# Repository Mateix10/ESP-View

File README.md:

# ESP-View
This is a music visualiser + DAC that does exactly that - it plays the music through USB, and visualises it.

<sub>Also, a better name will be much appreciated :)</sub>

## PCB
The PCB is designed in kicad.

## Case
The case features a screw and a little groove where the PCB slides.
It has a slick, modern, round design.

Designed in Fusion 360.

## Firmware 
The whole thing is powered by a ESP32, paired with a PCM5102A DAC.
The firmware is written in Arduino IDE

To interface with the ESP32, you need to install board support in Arduino IDE.
You can do that by going to File -> Preferences -> Additional Board Manager URLs, and add https://espressif.github.io/arduino-esp32/package_esp32_index.json

After that, go to Tools -> Board -> Boards Manager. Search for esp32 and install "esp32" by Espressif.

**WARNING**: Version 3.x is required for proper TinyUSB audio support.

Required libraries:
- NeoPixelBus by Makuna
- arduinoFFT
- TinyUSB (Usually bundled with the EPS32 Arduino Core)

All of these can be installed through the Arduino IDE's library manager.

The Firmware isn't currently tested.

## BOM
| Name | Cost |Link|
|--------|--------|--------|
| 1000uF Electrolytic Capacitor | $0.48 |https://www.optimusdigital.ro/ro/componente-electronice-condensatoare/3004-condensator-electrolitic-de-1000-uf-la-35-v.html|
| LED Matrix | $24.98 |https://www.superlightingled.com/5v-16x16-sk6812-rgbw-led-neopixel-matrix-display-screen-panel-51w-p-6835.html|
| DAC | $22.80 |https://www.optimusdigital.ro/ro/audio-altele/5658-modul-audio-stereo-dac-pcm5102a-cu-interfaa-pcm-32-bii-384-khz.html|
| Level Shifter| $3.19 |https://www.aliexpress.com/item/1005007123530432.html|
|ESP32-S3-DevKitC-1| $18.50 |https://www.aliexpress.com/item/1005003979778978.html|
|PCB|$1.74|-|

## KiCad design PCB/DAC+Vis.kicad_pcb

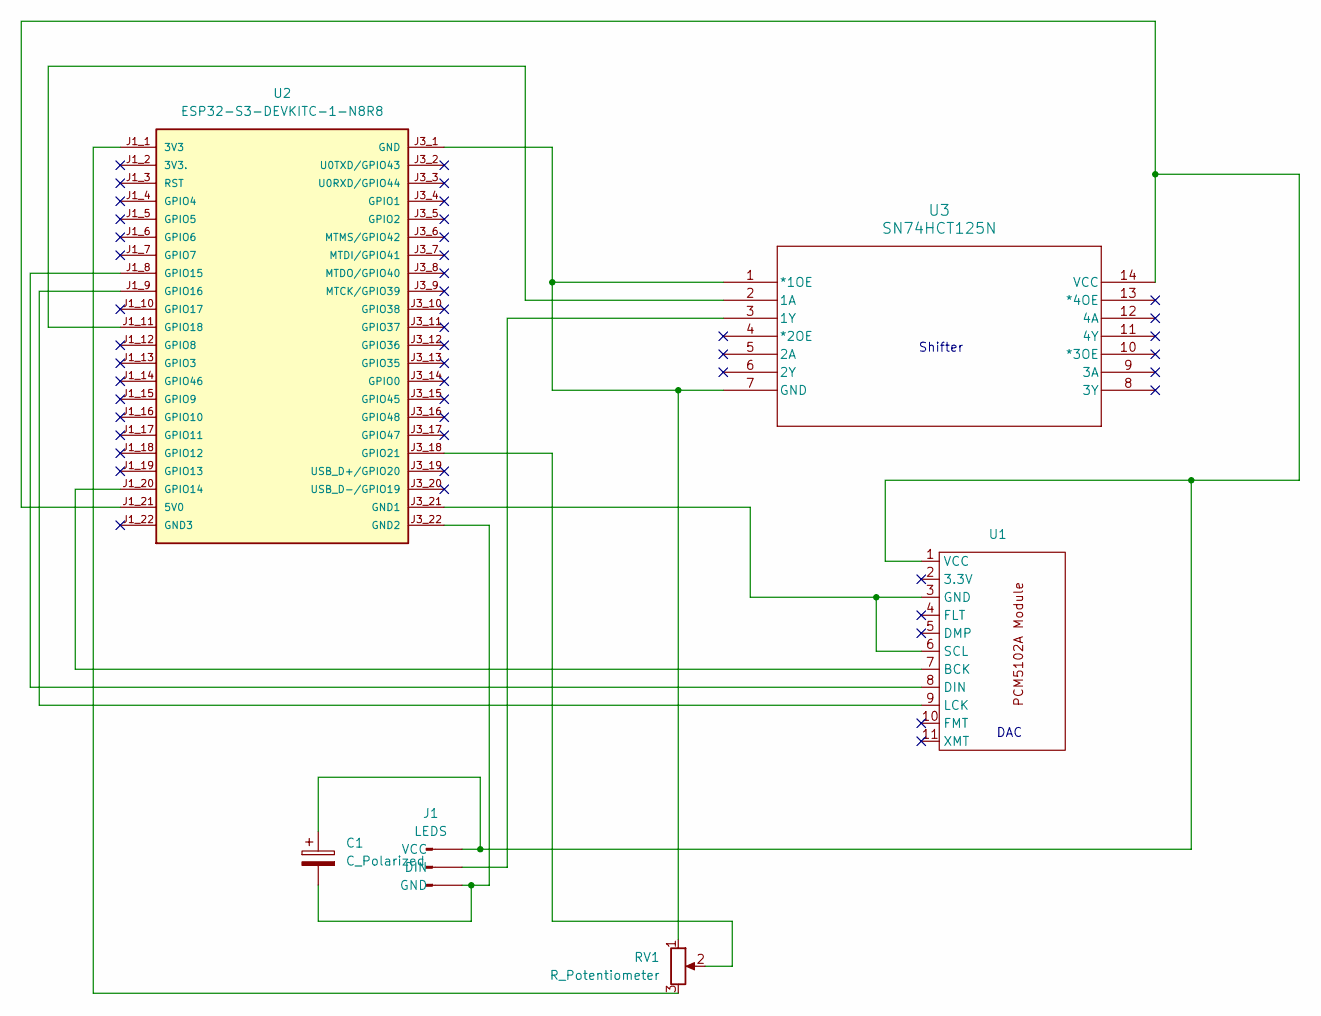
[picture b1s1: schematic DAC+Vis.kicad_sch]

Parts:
C1: C_Polarized; CP_Radial_D10.0mm_P5.00mm
J1: LEDS; SolderWire-4sqmm_1x03_P12mm_D3mm_OD6mm
RV1: R_Potentiometer; Potentiometer_Alps_RK097_Single_Horizontal
U1: PCM5102A Module
U2: ESP32-S3-DEVKITC-1-N8R8
U3: SN74HCT125N; N14

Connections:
unnamed: J1.2 (DIN), U3.3 (1Y)
unnamed: C1.2, J1.3 (GND), U2.J3_22 (GND2)
unnamed: C1.1, J1.1 (VCC), U1.1 (VCC), U2.J1_21 (5V0), U3.14 (VCC)
unnamed: U1.7 (BCK), U2.J1_20 (GPIO14)
unnamed: U1.8 (DIN), U2.J1_8 (GPIO15)
unnamed: U1.3 (GND), U1.6 (SCL), U2.J3_21 (GND1)
unnamed: U1.9 (LCK), U2.J1_9 (GPIO16)
unnamed: RV1.3, U2.J1_1 (3V3)
unnamed: RV1.1, U2.J3_1 (GND), U3.1 (*1OE), U3.7 (GND)
unnamed: U2.J1_11 (GPIO18), U3.2 (1A)
unnamed: RV1.2, U2.J3_18 (GPIO21)

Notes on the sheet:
Shifter
DAC

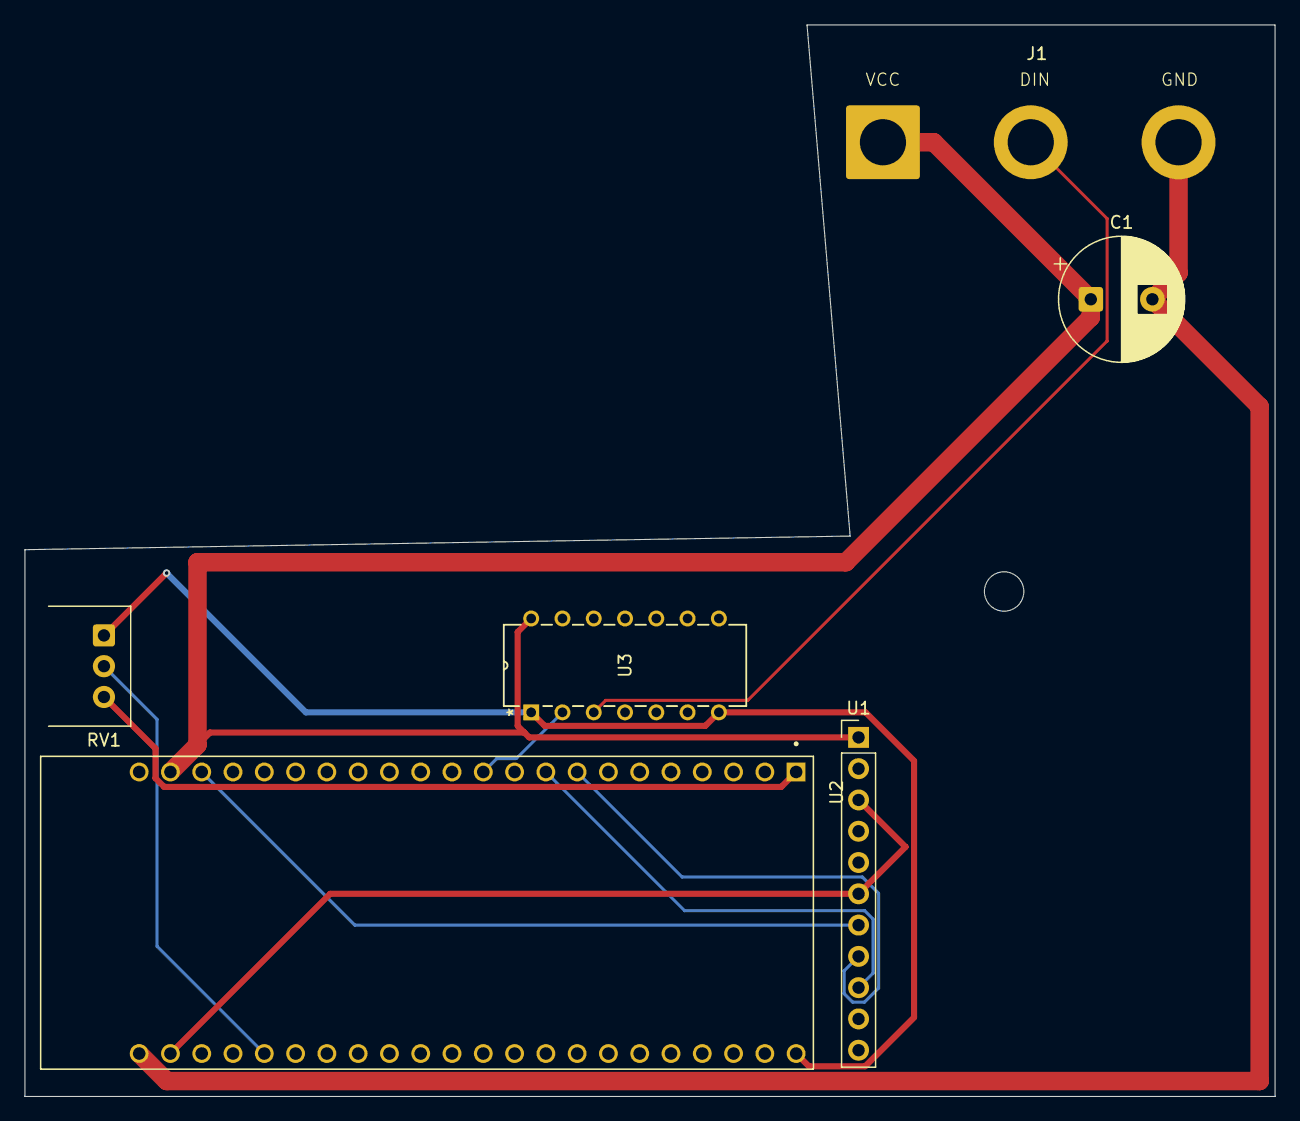
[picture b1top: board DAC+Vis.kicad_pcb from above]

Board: 2 copper layers, 101.5 x 87.0 mm, 6 parts (0 on the bottom side), 11 nets.

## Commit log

2026-03-09 Update .gitignore to add macOS files
    Added macOS system files.
2026-03-18 Enhance README with project details and specifications
    Added detailed description of the project, including case design and hardware specifications.
2026-03-18 Fix typo in README regarding ESP32 description
2026-03-18 Added images
2026-03-18 Added images to README
2026-03-18 Added image in README
2026-03-19 Fixed typo in README
2026-03-19 Add CAD and PCB files
2026-03-19 Fix images in README
2026-03-19 Added a render of the device
2026-03-19 Added BOM.csv
2026-03-19 Add BOM in README
2026-03-19 Added frimware
2026-03-19 Update README with frimware info
2026-03-19 Fix README
2026-03-19 Fix folder structure
2026-03-19 Add PCB to BOM
2026-05-24 Add build image to README
